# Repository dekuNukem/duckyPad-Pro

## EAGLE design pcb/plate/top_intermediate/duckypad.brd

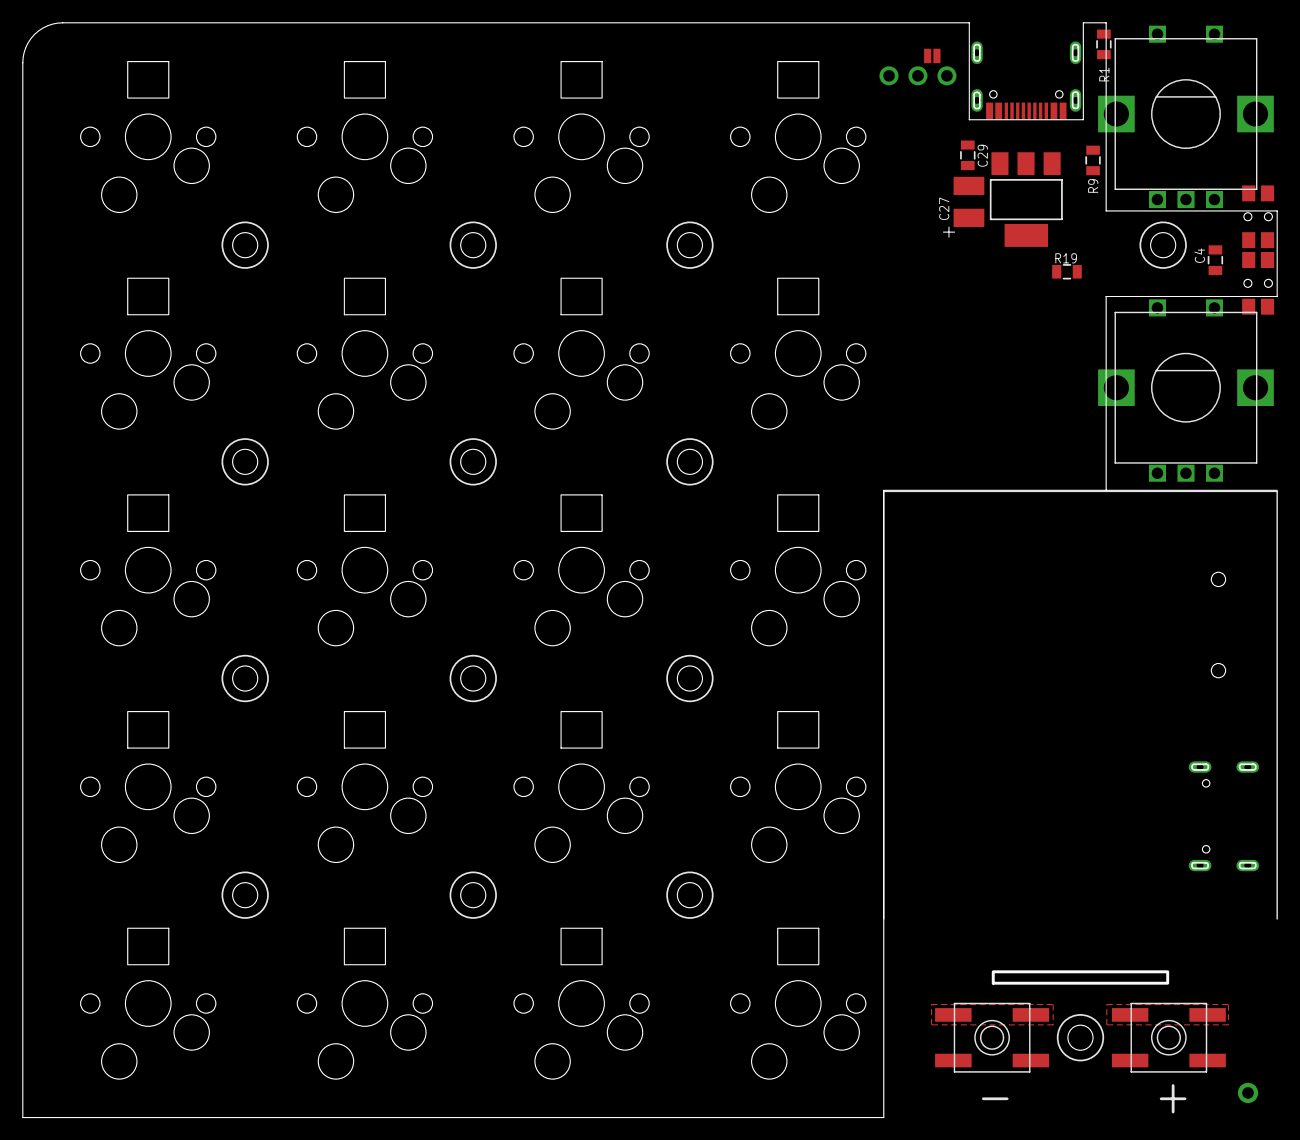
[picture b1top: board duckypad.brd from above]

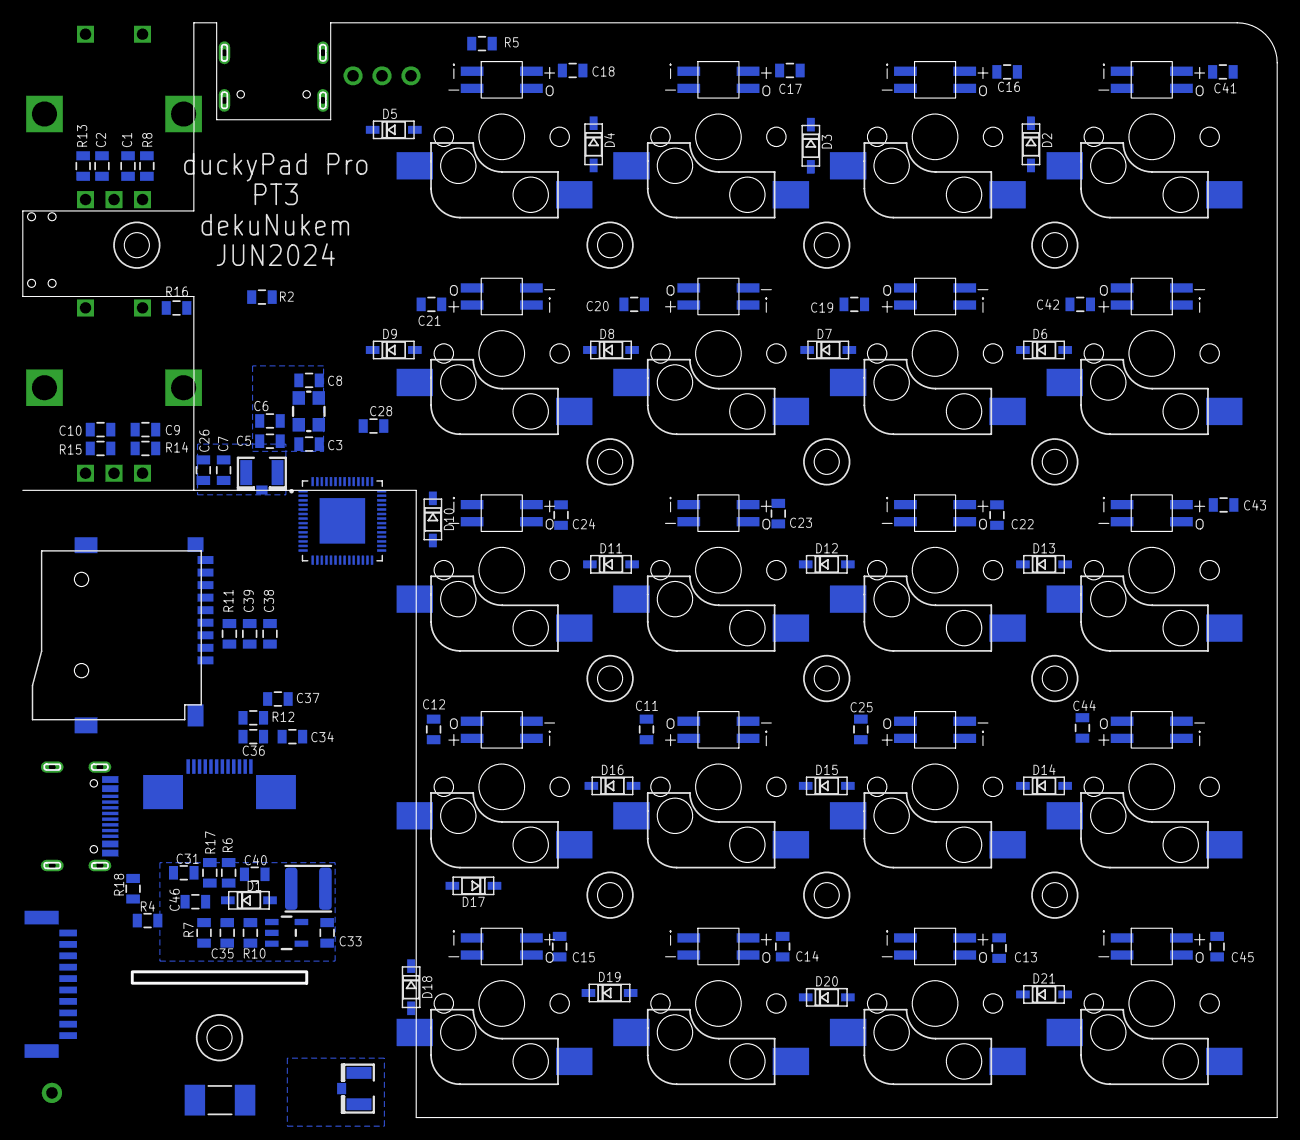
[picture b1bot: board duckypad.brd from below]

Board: 4 copper layers, 110.0 x 96.0 mm, 159 parts (88 on the bottom side), 100 nets.

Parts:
C1, C2, C4, C6, C9, C10, C11, C12, C13, C14, C15, C16, C17, C18, C19, C20, C21, C22, C23, C24, C25, C26, C28, C31, C37, C39, C40, C41, C42, C43, C44, C45: 100nF; 0805
C3, C8, C35: 12pF; 0805
C5, C7: 1uF; 0805
C27: 100uF; C1210
C29, C33, C34, C36, C38, C46: 4.7uF; 0805
D1, D2, D3, D4, D5, D6, D7, D8, D9, D10, D11, D12, D13, D14, D15, D16, D17, D18, D19, D20, D21: 1N4148; ADAFRUIT_CHANGED_SOD-123
IC2: REG1117; SOT223
JP1: JUMPER-SMT_2_NO_NO-SILK; SMT-JUMPER_2_NO_NO-SILK
JP2: 1X03-CLEANBIG
JP3: 1X01-CLEANBIG
L2: 4.7uH; L4030
LED_R1C1, LED_R1C2, LED_R1C3, LED_R1C4, LED_R2C1, LED_R2C2, LED_R2C3, LED_R2C4, LED_R3C1, LED_R3C2, LED_R3C3, LED_R3C4, LED_R4C1, LED_R4C2, LED_R4C3, LED_R4C4, LED_R5C1, LED_R5C2, LED_R5C3, LED_R5C4: WS2812B; REVERSE_MNT
R1, R9: 5.1K; 0805
R2, R10: 62K; 0805
R3: R2010
R4, R18: 470; 0805
R5, R11, R12, R16, R17: 10K; 0805
R6, R7: 510K; 0805
R8, R13, R14, R15: 5K1; 0805
R19: DNP; 0805
SD1: TF-HOLDER; TF-PULL
SW1, SW2: SPST_TACT-EVQQ2; EVQ-Q2
SW3, SW4: 324_SW324_SWITCH_FOOT_HOLE; 342_SWICH_FOOT_HOLE
SW21, SW22: EC12E_SW; ALPS_EC12E_SW
SWR1C1, SWR1C2, SWR1C3, SWR1C4, SWR2C1, SWR2C2, SWR2C3, SWR2C4, SWR3C1, SWR3C2, SWR3C3, SWR3C4, SWR4C1, SWR4C2, SWR4C3, SWR4C4, SWR5C1, SWR5C2, SWR5C3, SWR5C4: KAILH_SWITCH_SOCKET_KAILH_SWITCH_SOCKET; KAILH_SWITCH_SOCKET_SWITCH_SOCKET
U1, U2: USBC_16P; USBC_16P_FOOT
U3: ESP32-S3FN8; QFN40P700X700X90-57N
U$2: OLED_OLED128; OLED_LUL_UG-2864HSWEG01_1.3_WRAPAROUND
U$3: SH10P; DUCKYPAD_SM12B-SSR-H-TB
U$7, U$8, U$9, U$10, U$11, U$12, U$13, U$14, U$15, U$16, U$17, U$20, U$21, U$22: M2_SCREW_DEV; M2_SCREW_FOOT
U$19: V_REG_TPS61040SMD; SOT23-5
X1, X2: U.FL
Y1: 16MHz_12pF; CRYSTAL-SMD-3.2X2.5MM

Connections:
12V: C31.2, C35.2, C40.2, C46.2, D1.C, R7.1, U$2.2, U$2.11
+3V3: C5.2, C6.2, C7.2, C11.2, C12.2, C13.2, C14.2, C15.2, C16.2, C17.2, C18.2, C19.2, C20.2, C21.2, C22.2, C23.2, C24.2, C25.2, C26.2, C27.1, C28.2, C33.2, C36.2, C37.2, C38.2, C39.2, C41.2, C42.2, C43.2, C44.2, C45.2, IC2.2, IC2.4, L2.1, LED_R1C1.VDD, LED_R1C2.VDD, LED_R1C3.VDD, LED_R1C4.VDD, LED_R2C1.VDD, LED_R2C2.VDD, LED_R2C3.VDD, LED_R2C4.VDD, LED_R3C1.VDD, LED_R3C2.VDD, LED_R3C3.VDD, LED_R3C4.VDD, LED_R4C1.VDD, LED_R4C2.VDD, LED_R4C3.VDD, LED_R4C4.VDD, LED_R5C1.VDD, LED_R5C2.VDD, LED_R5C3.VDD, LED_R5C4.VDD, R2.1, R11.1, R12.2, R16.2, SD1.4, U3.2, U3.3, U3.20, U3.46, U3.55, U3.56, U$2.4, U$3.3, U$19.4, U$19.5
AUX_DN: U1.A7, U1.B7, U3.21
AUX_DP: U1.A6, U1.B6, U3.22
CARD_DET: SD1.9, U3.11
CC_BUSY: R4.1, R18.1, U3.27, U$3.4
COL0: SWR1C1.1, SWR2C1.1, SWR3C1.1, SWR4C1.1, SWR5C1.1, U3.48
COL1: SWR1C2.1, SWR2C2.1, SWR3C2.1, SWR4C2.1, SWR5C2.1, U3.47
COL2: SWR1C3.1, SWR2C3.1, SWR3C3.1, SWR4C3.1, SWR5C3.1, U3.44
COL3: SWR1C4.1, SWR2C4.1, SWR3C4.1, SWR4C4.1, SWR5C4.1, U3.43
DC: U3.17, U$2.8
GND: C1.1, C2.1, C3.2, C4.2, C5.1, C6.1, C7.1, C8.2, C9.1, C10.1, C11.1, C12.1, C13.1, C14.1, C15.1, C16.1, C17.1, C18.1, C19.1, C20.1, C21.1, C22.1, C23.1, C24.1, C25.1, C26.1, C27.2, C28.1, C29.1, C31.1, C33.1, C34.1, C36.1, C37.1, C38.1, C39.1, C40.1, C41.1, C42.1, C43.1, C44.1, C45.1, C46.1, IC2.1, LED_R1C1.GND, LED_R1C2.GND, LED_R1C3.GND, LED_R1C4.GND, LED_R2C1.GND, LED_R2C2.GND, LED_R2C3.GND, LED_R2C4.GND, LED_R3C1.GND, LED_R3C2.GND, LED_R3C3.GND, LED_R3C4.GND, LED_R4C1.GND, LED_R4C2.GND, LED_R4C3.GND, LED_R4C4.GND, LED_R5C1.GND, LED_R5C2.GND, LED_R5C3.GND, LED_R5C4.GND, R1.2, R5.1, R6.1, R9.2, R10.2, R17.1, SD1.6, SD1.S1, SD1.S2, SD1.S3, SD1.S4, SW1.A, SW1.A', SW2.A, SW2.A', SW3.P$1, SW3.P$4, SW4.P$1, SW4.P$4, SW21.C, SW21.E, SW22.C, SW22.E, U1.A1B12, U1.B11A12, U1.P$13, U1.P$14, U1.P$15, U1.P$16, U2.A1B12, U2.B11A12, U2.P$13, U2.P$14, U2.P$15, U2.P$16, U3.57, U$2.1, U$2.12, U$2.31, U$2.32, U$3.2, U$3.FIT@1, U$3.FIT@2, U$19.2, X1.1, X1.2, X2.1, X2.2, Y1.2, Y1.4
MOSI: U3.15, U$2.10
unnamed: JP1.1, JP2.1, U2.A4B9, U2.B4A9
unnamed: LED_R1C3.DIN, LED_R1C4.DOUT
unnamed: LED_R1C2.DIN, LED_R1C3.DOUT
unnamed: LED_R1C1.DIN, LED_R1C2.DOUT
unnamed: LED_R1C1.DOUT, LED_R2C1.DIN
unnamed: LED_R2C1.DOUT, LED_R2C2.DIN
unnamed: LED_R2C2.DOUT, LED_R2C3.DIN
unnamed: C34.2, U$2.3
unnamed: LED_R2C3.DOUT, LED_R2C4.DIN
unnamed: R6.2, U$2.5
unnamed: LED_R2C4.DOUT, LED_R3C4.DIN
unnamed: LED_R3C3.DIN, LED_R3C4.DOUT
unnamed: LED_R3C2.DIN, LED_R3C3.DOUT
unnamed: C9.2, R14.1, U3.9
unnamed: LED_R3C1.DIN, LED_R3C2.DOUT
unnamed: LED_R3C1.DOUT, LED_R4C1.DIN
unnamed: LED_R4C1.DOUT, LED_R4C2.DIN
unnamed: LED_R4C2.DOUT, LED_R4C3.DIN
unnamed: LED_R4C3.DOUT, LED_R4C4.DIN
unnamed: LED_R4C4.DOUT, LED_R5C4.DIN
unnamed: LED_R5C3.DIN, LED_R5C4.DOUT
unnamed: LED_R5C2.DIN, LED_R5C3.DOUT
unnamed: LED_R5C1.DIN, LED_R5C2.DOUT
unnamed: C8.1, U3.54, Y1.1
unnamed: C3.1, U3.53, Y1.3
unnamed: U3.1, X1.3
unnamed: D5.A, SWR1C4.2
unnamed: SW4.P$2, SW4.P$3, SW22.D, U3.5
unnamed: LED_R1C4.DIN, R5.2, U3.52
unnamed: SW1.B, SW1.B', U3.23
unnamed: R1.1, U2.B5
unnamed: R4.2, U1.A5
unnamed: R9.1, U2.A5
unnamed: R8.2, SW22.A
unnamed: R13.2, SW22.B
unnamed: D1.A, L2.2, U$19.1
unnamed: C1.2, R8.1, U3.6
unnamed: C35.1, R7.2, R10.1, U$19.3
unnamed: C2.2, R13.1, U3.7
unnamed: R16.1, R19.1, SW21.D, U3.8
unnamed: R15.2, SW21.B
unnamed: R11.2, SD1.2
unnamed: D4.A, SWR1C3.2
unnamed: D3.A, SWR1C2.2
unnamed: D2.A, SWR1C1.2
unnamed: D9.A, SWR2C4.2
unnamed: R14.2, SW21.A
unnamed: C10.2, R15.1, U3.10
unnamed: D8.A, SWR2C3.2
unnamed: D7.A, SWR2C2.2
unnamed: D6.A, SWR2C1.2
unnamed: D10.A, SWR3C4.2
unnamed: D11.A, SWR3C3.2
unnamed: D12.A, SWR3C2.2
unnamed: D13.A, SWR3C1.2
unnamed: D17.A, SWR4C4.2
unnamed: D16.A, SWR4C3.2
unnamed: D15.A, SWR4C2.2
unnamed: D14.A, SWR4C1.2
unnamed: D18.A, SWR5C4.2
unnamed: D19.A, SWR5C3.2
unnamed: D20.A, SWR5C2.2
unnamed: D21.A, SWR5C1.2
unnamed: SW2.B, SW2.B', U3.24
unnamed: C29.2, IC2.3, JP1.2, JP2.2, U1.A4B9, U1.B4A9, U$3.1
unnamed: U3.36, U$3.5
unnamed: U3.37, U$3.6
unnamed: U3.38, U$3.7
unnamed: U3.39, U$3.8
unnamed: R3.1, X2.3
unnamed: U3.50, U$3.9
unnamed: JP3.1, U3.49, U$3.10
unnamed: R18.2, U1.B5
OLED_CS: R12.1, U3.19, U$2.6
OLED_RESET: R17.2, U3.18, U$2.7
RESET: C4.1, R2.2, R19.2, SW3.P$2, SW3.P$3, U3.4
ROW0: D2.C, D3.C, D4.C, D5.C, U3.51
ROW1: D6.C, D7.C, D8.C, D9.C, U3.45
ROW2: D10.C, D11.C, D12.C, D13.C, U3.42
ROW3: D14.C, D15.C, D16.C, D17.C, U3.41
ROW4: D18.C, D19.C, D20.C, D21.C, U3.40
SCLK: U3.16, U$2.9
SD_CLK: SD1.5, U3.13
SD_CMD: SD1.3, U3.14
SD_D0: SD1.7, U3.12
USB_DN: U2.A7, U2.B7, U3.25
USB_DP: U2.A6, U2.B6, U3.26

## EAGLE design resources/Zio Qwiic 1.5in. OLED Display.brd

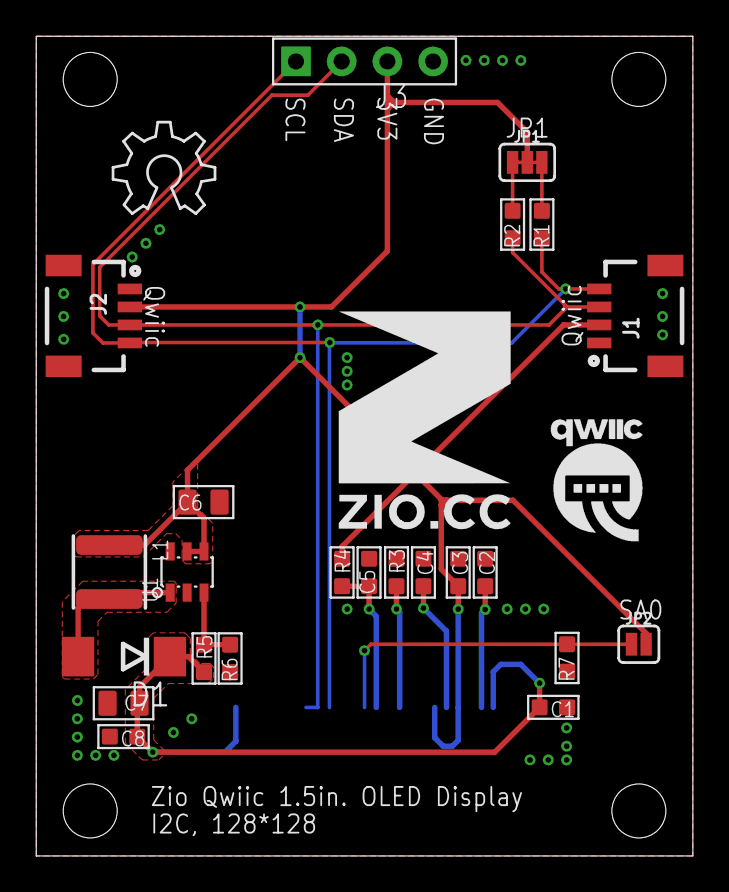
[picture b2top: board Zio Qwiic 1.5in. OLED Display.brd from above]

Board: 2 copper layers, 36.5 x 45.5 mm, 27 parts (1 on the bottom side), 14 nets.

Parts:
C1, C2: 4.7uF ±10% 25V; C0603
C3, C4, C5, C8: 100nF ±10% 50V; C0603
C6, C7: 22uF ±20% 25V; C0805
D1: SS14; DO-214AC
J1, J2: JST-SH-4P-1.0; JST-SH-4P
J3: 4P-65/35MIL
JP1: SMT-JUMPER_3_2-NC_TRACE
JP2: JUMPER-SMT_2_NC_PASTE_NOCREM; SMT-JUMPER_2_NC_PASTE_SILK_NOCREM
L1: PRS4018-4R7MT; L4030
OLED1: OLED_MODULE_1.5IN_128128; OLED_MODULE_1.5IN_128*128
R1, R2: 4.7K ±1%; R0603
R3: 1.2M ±1%; R0603
R4, R6, R7: 10K ±1%; R0603
R5: 240K ±1%; R0603
U1: SX1308; SOT23-6
U$4: 12MM
U$5: QWIIC-LOGO-MEDIUM
U$6: OSHW_6X200_NOTEXT

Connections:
+3V3: C3.2, C6.1, J1.2, J2.2, J3.3, JP1.2, JP2.2, L1.1, OLED1.5, OLED1.7, R4.1, U1.4, U1.5
GND: C1.1, C2.1, C3.1, C4.1, C5.2, C6.2, C7.2, C8.2, J1.1, J1.NC1, J1.NC2, J2.1, J2.NC1, J2.NC2, J3.4, OLED1.1, OLED1.4, OLED1.8, OLED1.9, OLED1.11, OLED1.14, OLED1.15, OLED1.19, OLED1.20, OLED1.21, OLED1.22, OLED1.23, OLED1.25, R3.1, R6.1, R7.1, U1.2
unnamed: JP1.3, R1.2
unnamed: R5.1, R6.2, U1.3
unnamed: JP1.1, R2.2
unnamed: C5.1, OLED1.12, R4.2
unnamed: OLED1.10, R3.2
unnamed: C4.2, OLED1.6
unnamed: C2.2, OLED1.3
SA0: JP2.1, OLED1.13, R7.2
SCL: J1.4, J2.4, J3.1, OLED1.16, R1.1
SDA: J1.3, J2.3, J3.2, OLED1.17, OLED1.18, R2.1
SW: D1.A, L1.2, U1.1
VPP: C1.2, C7.1, C8.1, D1.C, OLED1.2, OLED1.24, R5.2

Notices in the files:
parts and their libraries:
SparkFun-Clocks: Licensing: Creative Commons ShareAlike 4.0 International - https://creativecommons.org/licenses/by-sa/4.0
